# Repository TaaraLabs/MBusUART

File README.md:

M-Bus UART
==========

Simple M-Bus (Meter-Bus) master to UART converter

[Official WebSite](https://taaralabs.eu/mu1)

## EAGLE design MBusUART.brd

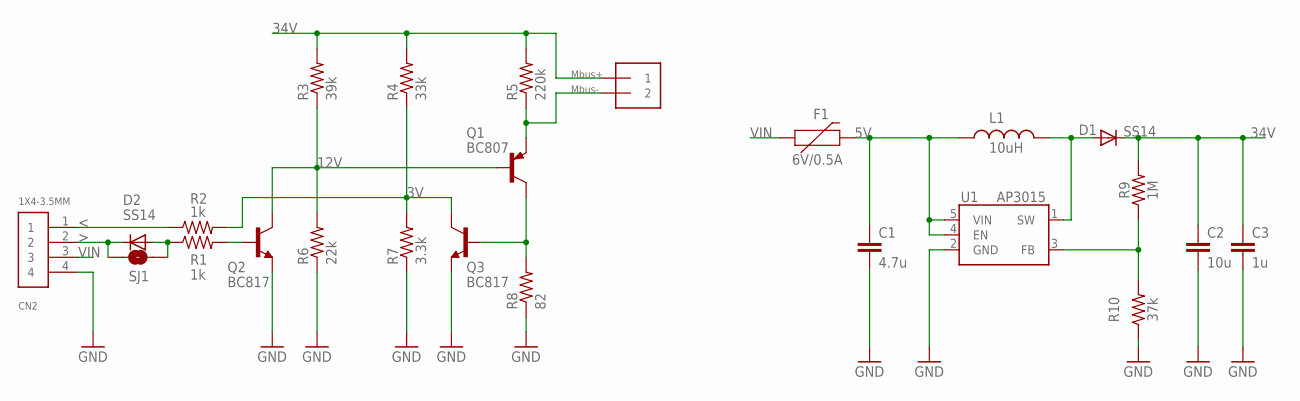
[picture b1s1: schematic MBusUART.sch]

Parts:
C1: 4.7u; 0805
C2: 10u; 1206
C3: 1u; 1206
CN2: 1X4-3.5MM; 1X04-3.5MM
D1, D2: SS14; SOD-123
F1: 6V/0.5A; 1206
J1: 1X2-3.5MM
L1: 10uH; CR54
Q1: BC807; SOT23-BEC
Q2, Q3: BC817; SOT23-BEC
R1, R2: 1k; 0805
R3: 39k; 0805
R4: 33k; 0805
R5: 220k; 1206
R6: 22k; 0805
R7: 3.3k; 0805
R8: 82; 1206
R9: 1M; 0805
R10: 37k; 0805
SJ1: SOLDERJUMPERNO; SJ_2S-NO
U1: AP3015; SOT-23-5

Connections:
3V: Q3.C, R2.2, R4.1, R7.2
5V: C1.1, F1.2, L1.P$1 (1), U1.4 (EN), U1.5 (VIN)
12V: Q1.B, Q2.C, R3.1, R6.2
34V: C2.1, C3.1, D1.C, J1.1, R3.2, R4.2, R5.2, R9.2
<: CN2.1, R2.1
>: CN2.2, D2.C, SJ1.1
GND: C1.2, C2.2, C3.2, CN2.4, Q2.E, Q3.E, R6.1, R7.1, R8.1, R10.1, U1.2 (GND)
MBUS-: J1.2, Q1.E, R5.1
unnamed: Q1.C, Q3.B, R8.2
unnamed: R9.1, R10.2, U1.3 (FB)
unnamed: D1.A, L1.P$2 (2), U1.1 (SW)
unnamed: D2.A, R1.1, SJ1.2
unnamed: Q2.B, R1.2
VIN: CN2.3, F1.1

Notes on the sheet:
Mbus+
Mbus-

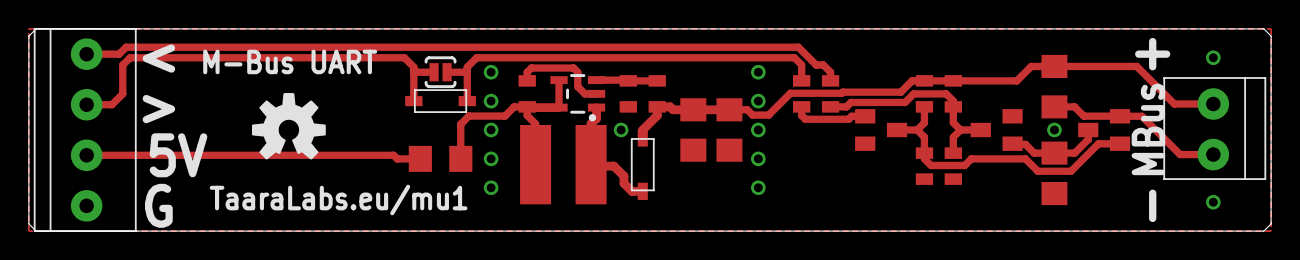
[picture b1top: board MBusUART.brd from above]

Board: 2 copper layers, 86.0 x 14.0 mm, 26 parts (1 on the bottom side), 14 nets.

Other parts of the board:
U$1, U$2: OSHW-LOGO-M

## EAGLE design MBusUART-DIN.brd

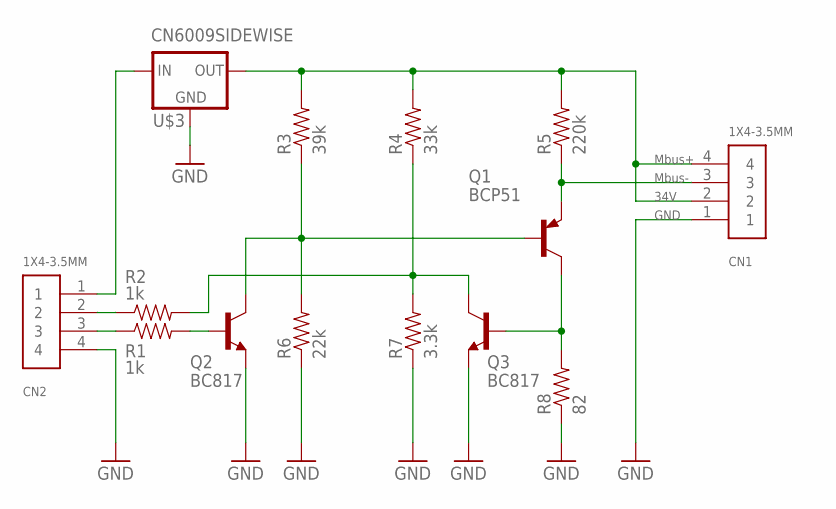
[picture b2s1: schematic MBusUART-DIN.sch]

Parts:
CN1, CN2: 1X4-3.5MM; 1X04-3.5MM
Q1: BCP51; SOT223
Q2, Q3: BC817; SOT23-BEC
R1, R2: 1k; 0805
R3: 39k; 0805
R4: 33k; 0805
R5: 220k; 1206
R6: 22k; 0805
R7: 3.3k; 0805
R8: 82; 1206
U$3: CN6009SIDEWISE; CN6009-SIDEWISE

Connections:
34V: CN1.2, CN1.4, R3.2, R4.2, R5.2, U$3.P$4 (OUT), U$3.P$41 (OUT)
B: Q1.1 (B), Q2.C, R3.1, R6.2
GND: CN1.1, CN2.4, Q2.E, Q3.E, R6.1, R7.1, R8.1, U$3.P$1 (GND), U$3.P$2 (GND), U$3.P$11 (GND), U$3.P$21 (GND)
MBUS-: CN1.3, Q1.3 (E), R5.1
unnamed: Q3.C, R2.2, R4.1, R7.2
unnamed: CN2.1, U$3.P$3 (IN), U$3.P$31 (IN)
unnamed: Q1.2 (C), Q1.4 (C), Q3.B, R8.2
unnamed: CN2.2, R2.1
unnamed: CN2.3, R1.1
unnamed: Q2.B, R1.2

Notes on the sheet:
Mbus+
Mbus-

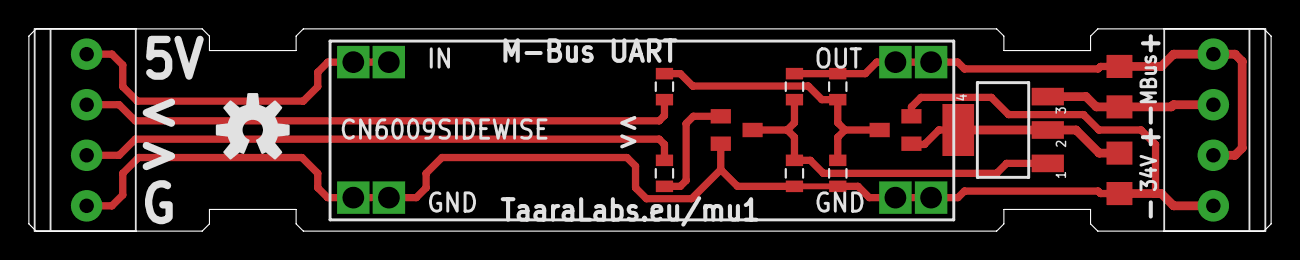
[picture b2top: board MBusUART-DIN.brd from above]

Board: 2 copper layers, 86.0 x 14.0 mm, 16 parts (1 on the bottom side), 10 nets.

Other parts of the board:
U$1, U$2: OSHW-LOGO-M

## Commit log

2019-01-24 added README.mD
2019-01-24 added Eagle files for DIN version
2019-01-24 added pictures of DIN version
2019-01-24 added gerbers for DIN version
2019-12-23 Correct pictures
2020-01-03 Added design files for the generic version

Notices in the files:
parts and their libraries:
SparkFun: Licensing: CC v3.0 Share-Alike You are welcome to use this library for commercial purposes.
SparkFun-Capacitors: Licensing: Creative Commons ShareAlike 4.0 International - https://creativecommons.org/licenses/by-sa/4.0
